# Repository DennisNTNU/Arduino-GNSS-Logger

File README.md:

## Arduino GNSS Logger

Readme to be written

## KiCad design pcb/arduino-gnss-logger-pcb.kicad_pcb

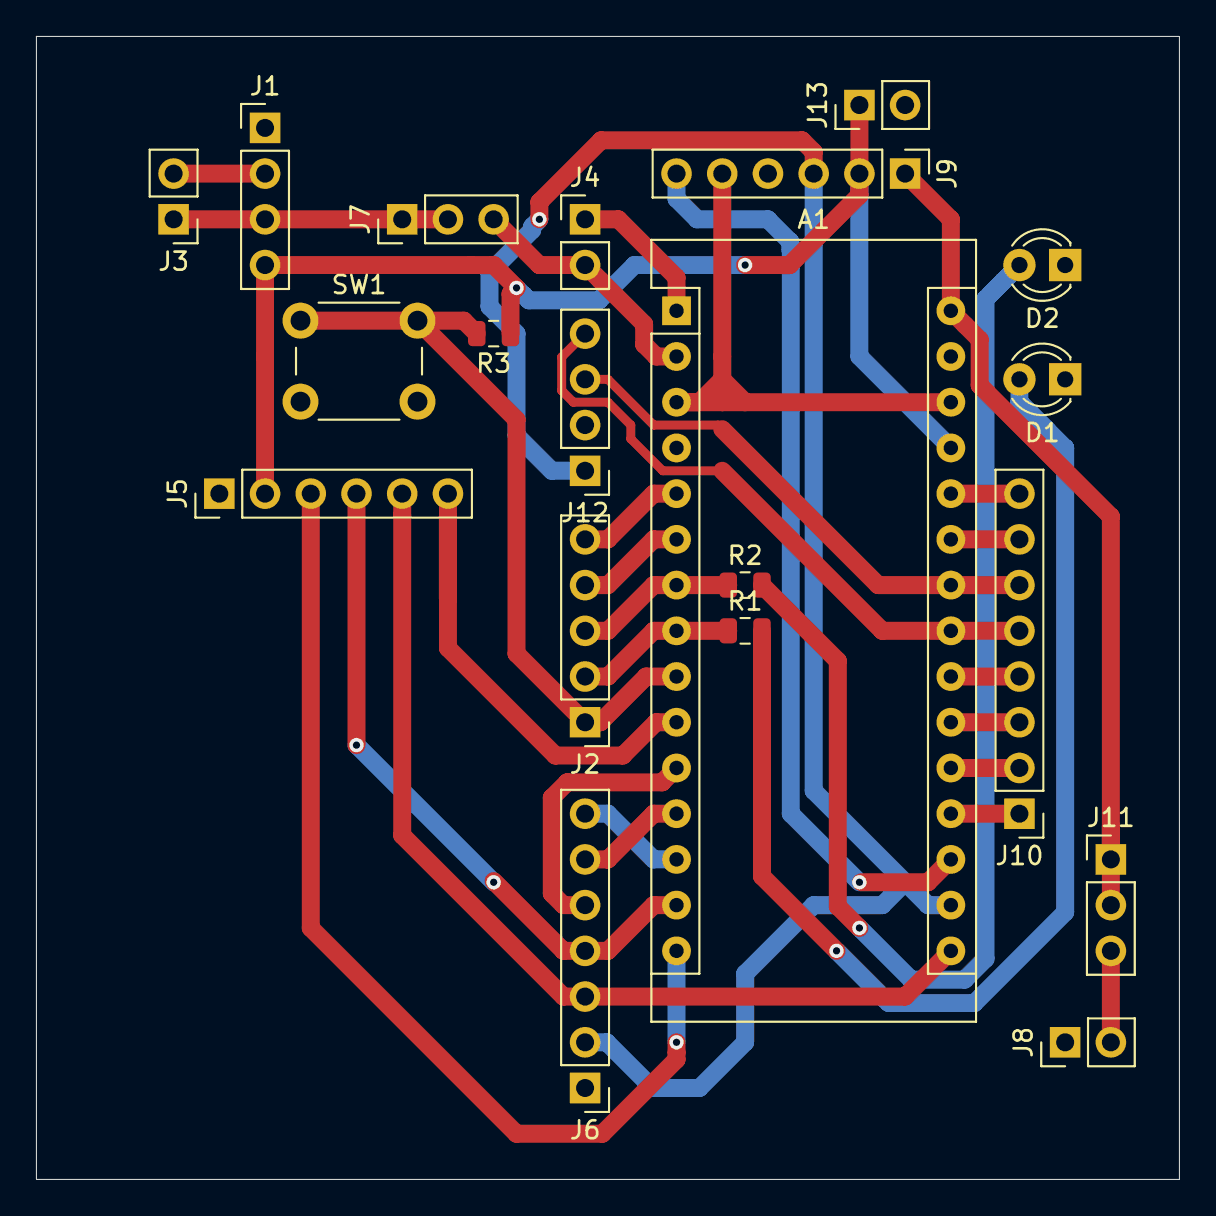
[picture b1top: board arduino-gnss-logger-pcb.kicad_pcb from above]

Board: 2 copper layers, 63.5 x 63.5 mm, 20 parts (0 on the bottom side), 33 nets.

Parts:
A1: Arduino_Nano_v2.x; Arduino_Nano
D1, D2: LED; LED_D3.0mm
J1: GNSSModule; PinHeader_1x04_P2.54mm_Vertical
J2: GPIO1; PinHeader_1x05_P2.54mm_Vertical
J3: GNSSUARTOut; PinHeader_1x02_P2.54mm_Vertical
J4: UART; PinHeader_1x02_P2.54mm_Vertical
J5: SDCardReader; PinHeader_1x06_P2.54mm_Vertical
J6: OledScreen; PinHeader_1x07_P2.54mm_Vertical
J7: UARTJumper; PinHeader_1x03_P2.54mm_Vertical
J8: BatteryInput; PinHeader_1x02_P2.54mm_Vertical
J9: IO; PinHeader_1x06_P2.54mm_Vertical
J10: GPIO2; PinHeader_1x08_P2.54mm_Vertical
J11: BatteryJumper; PinHeader_1x03_P2.54mm_Vertical
J12: OledScreen_I2C; PinHeader_1x04_P2.54mm_Vertical
J13: 5V Header; PinHeader_1x02_P2.54mm_Vertical
R1, R2, R3: R; R_0805_2012Metric
SW1: SW_Push_Dual; SW_PUSH_6mm

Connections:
/D6: A1.9, J2.1, R3.2, SW1.1
GNDPWR: A1.4, A1.29, D1.1, D2.1, J1.1, J5.1, J6.1, J8.1, J9.4, J12.2, J13.2, SW1.2
unnamed: A1.1, J4.1
unnamed: A1.2, J4.2, J7.3
unnamed: A1.5, J2.5
unnamed: A1.6, J2.4
unnamed: A1.7, J2.3, R2.1
unnamed: A1.8, J2.2, R1.1
unnamed: A1.10, J5.6
unnamed: A1.11, J6.5
unnamed: A1.12, J6.6
unnamed: A1.13, J6.7
unnamed: A1.14, J5.4, J6.4
unnamed: A1.15, J5.3
unnamed: A1.16, J5.5, J6.3
unnamed: A1.17, J6.2, J9.3, J12.1
unnamed: A1.18, J9.6
unnamed: A1.19, J10.1
unnamed: A1.20, J10.2
unnamed: A1.21, J10.3
unnamed: A1.22, J10.4
unnamed: A1.23, J10.5, J12.4
unnamed: A1.24, J10.6, J12.3
unnamed: A1.25, J10.7
unnamed: A1.26, J10.8
unnamed: A1.27, J1.4, J5.2, J9.2, J13.1, R3.1
unnamed: A1.3, A1.28, J9.5
unnamed: A1.30, J9.1, J11.1, J11.2
unnamed: D1.2, R1.2
unnamed: D2.2, R2.2
unnamed: J1.2, J3.2
unnamed: J1.3, J3.1, J7.1, J7.2
unnamed: J8.2, J11.3

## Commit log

2022-08-05 Add Arduino code
2022-08-05 Add log parser python script
2022-08-05 Add KiCad project files
2022-08-05 Add .gitignore
2023-01-08 Fix .csv case bug; add phybox app log parser
2024-03-02 Add option for data decimation; Fix parsing of western longitudes
2024-03-02 increase logger decimation from 2 to 3
2024-03-02 Update phybox app gnss log parsing
2024-03-02 Add parsing for logs from flightsradar24 website
2024-09-13 Add parsing from gopro timelapse images
2025-11-30 Small fixes: support southern hemisphere coords, Data placement on screen
2025-12-02 Add si7021 sensor, read data nd print to screen
